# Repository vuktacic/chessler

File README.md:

# chessler/chessbot
A robot that plays chess. It uses a camera to detect Aruco tags on the board corners and the pieces, and an electromagnet on a gantry under the board to move the pieces. Designed for Hack Club's Outpost program. I wanted to do something involving Aruco tags outside of FRC, and this seemed like a good project to make.

## Structure
- [./assets](./assets): Repo images
- [./cad](./cad): 3d models
- [./core](./core): esp32 firmware
- [./pcb](./pcb): Kicad design files.
- [./vision](./vision): Computer side vision code
- [./bom.csv](./bom.csv): Bill of materials
- [./po.csv](./po.csv): Purchase order
- [./JOURNAL.md](./JOURNAL.md): Project journal

View the PCB on KiCanvas:  

## CAD

## Schematic

## PCB

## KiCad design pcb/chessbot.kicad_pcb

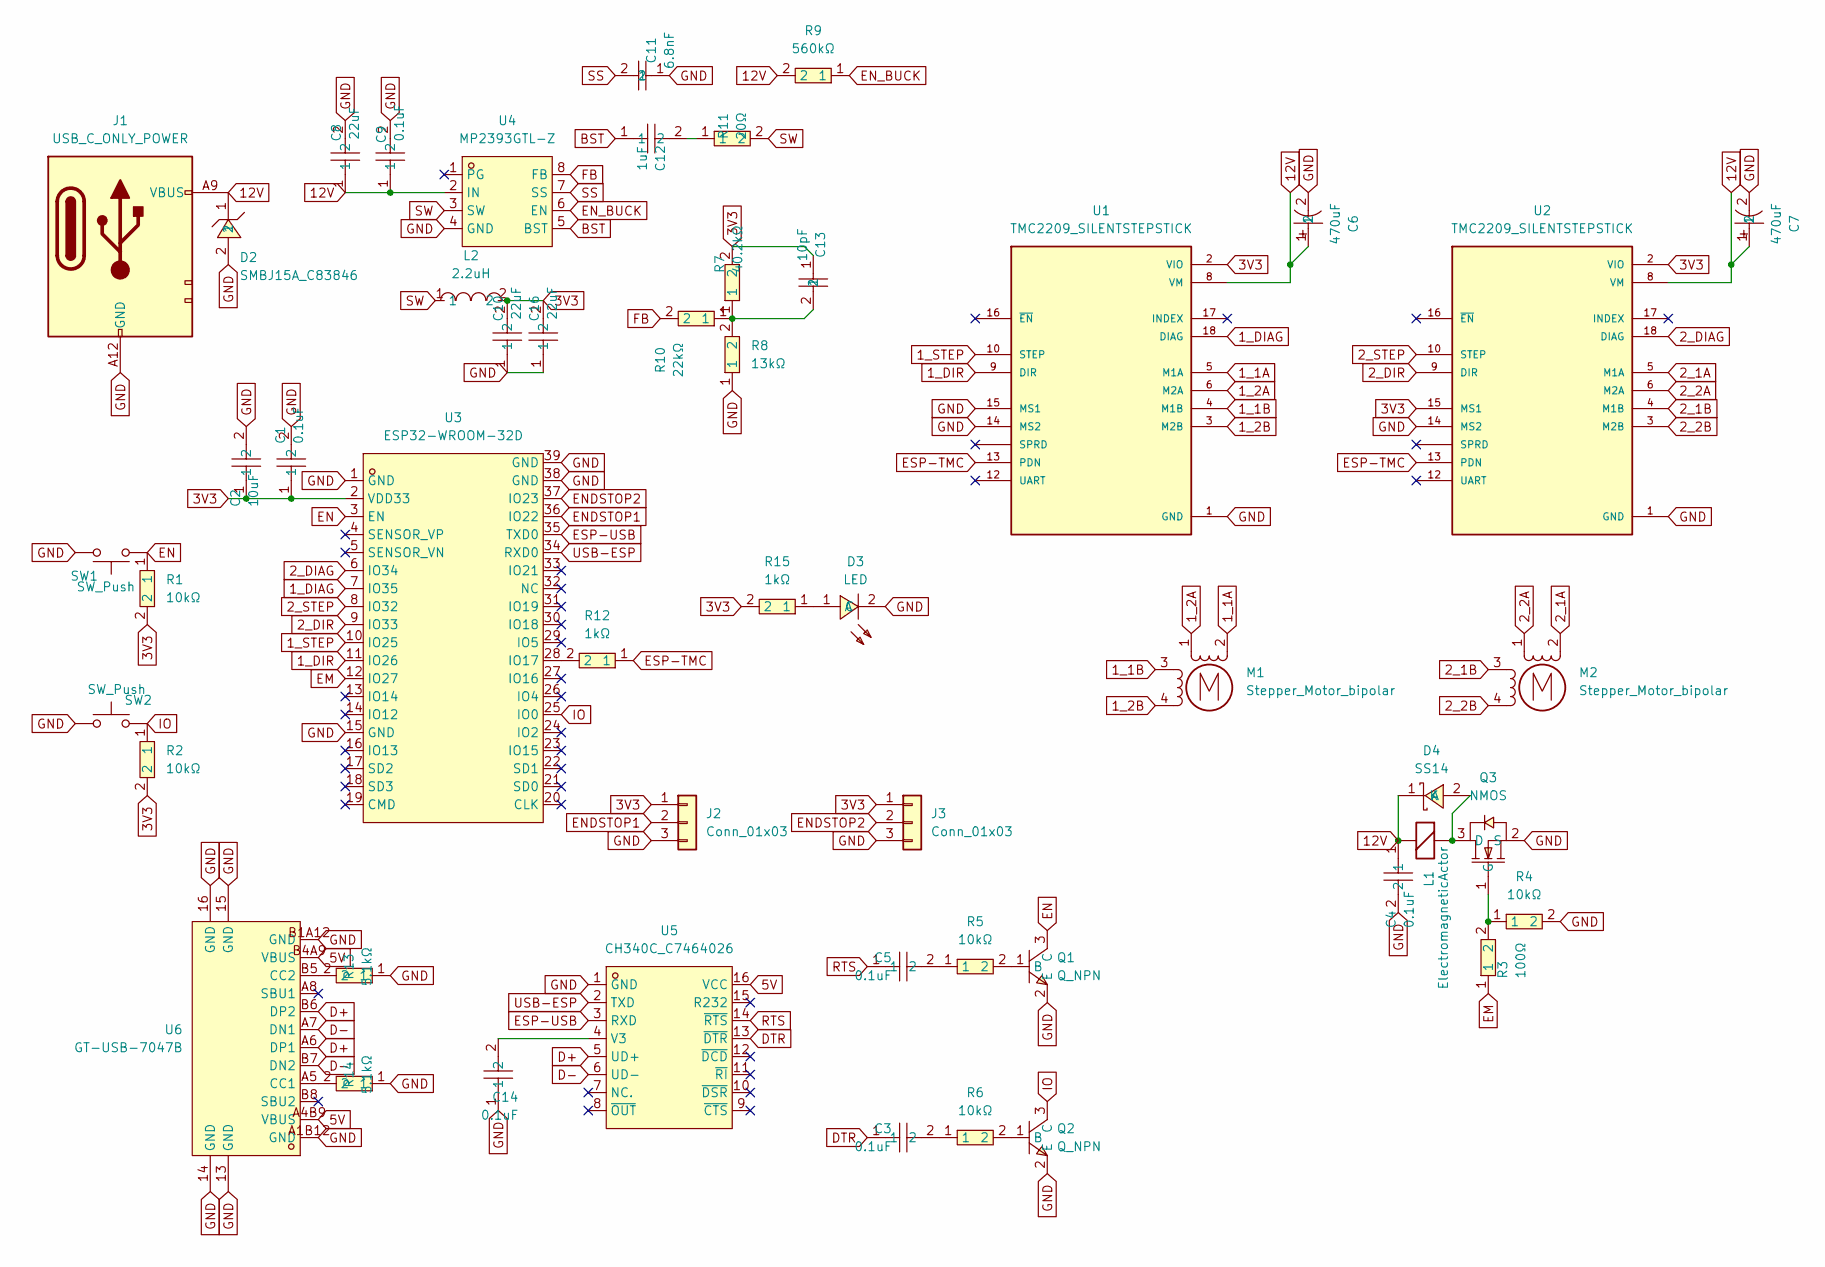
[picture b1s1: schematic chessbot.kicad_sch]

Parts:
C1, C3, C4, C5, C9, C14: 0.1uF; C0603; MPN CC0603KRX7R9BB104; LCSC Part C14663
C2: 10uF; C0603; MPN CL10A106MA8NRNC; LCSC Part C96446
C6, C7: 470uF; CAP-SMD_BD10.0-L10.3-W10.3-FD; MPN RVT1V471M1010; LCSC Part C3350
C8, C10, C16: 22uF; C0805; MPN CL21A226MAQNNNE; LCSC Part C45783
C11: 6.8nF; C0603; MPN 0603B682K500NT; LCSC Part C1631
C12: 1uF; C0603; MPN CL10A105KB8NNNC; LCSC Part C15849
C13: 10pF; C0603; MPN CL10C100JB8NNNC; LCSC Part C1634
D2: SMBJ15A_C83846; SMB_L4.6-W3.6-LS5.3-RD; LCSC Part C83846
D3: LED; LED0603-R-RD_AMBER; MPN BL-HJC36G-AV-TRB; LCSC Part C165983
D4: SS14; SMA_L4.2-W2.6-LS5.0-RD_1; MPN SS14; LCSC Part C2480
J1: USB_C_ONLY_POWER; USB_C_PD_BOARD
J2, J3: Conn_01x03; JST_PH_B3B-PH-K_1x03_P2.00mm_Vertical
L1: ElectromagneticActor; JST_PH_B2B-PH-K_1x02_P2.00mm_Vertical
L2: 2.2uH; L0805; MPN CMI201209U2R2KT; LCSC Part C1043
M1, M2: Stepper_Motor_bipolar; JST_PH_B4B-PH-K_1x04_P2.00mm_Vertical
Q1, Q2: Q_NPN; SOT-23-3_L2.9-W1.3-P1.90-LS2.4-BR; MPN MMBT3904(RANGE:100-300); LCSC Part C20526
Q3: NMOS; SOT-23-3_L2.9-W1.3-P1.90-LS2.4-BR; MPN AO3400A; LCSC Part C20917
R1, R2, R4, R5, R6: 10kΩ; R0805; MPN 0805W8F1002T5E; LCSC Part C17414
R3: 100Ω; R0603; MPN 0603WAF1000T5E; LCSC Part C22775
R7: 40.2kΩ; R0603; MPN 0603WAF4022T5E; LCSC Part C12447
R8: 13kΩ; R0603; MPN 0603WAF1302T5E; LCSC Part C22797
R9: 560kΩ; R0603; MPN 0603WAF5603T5E; LCSC Part C23203
R10: 22kΩ; R0603; MPN 0603WAF2202T5E; LCSC Part C31850
R11: 20Ω; R0603; MPN 0603WAF200JT5E; LCSC Part C22950
R12, R15: 1kΩ; R0603; MPN 0603WAF1001T5E; LCSC Part C21190
R13, R14: 5.1kΩ; R0603; MPN 0603WAF5101T5E; LCSC Part C23186
SW1, SW2: SW_Push; SW_PUSH_6mm
U1, U2: TMC2209_SILENTSTEPSTICK; MODULE_TMC2209_SILENTSTEPSTICK_INTERNAL SILKSCREEN; PARTREV 1.20
U3: ESP32-WROOM-32D; WIFIM-SMD_39P-L25.5-W18.0-P1.27-BL; MPN ESP32-WROOM-32D-N4; LCSC Part C529578
U4: MP2393GTL-Z; SOT-583-8_L2.1-W1.2-P0.50-LS1.6-BL; MPN MP2393GTL-Z; LCSC Part C6674609
U5: CH340C_C7464026; SOP-16_L10.0-W3.9-P1.27-LS6.0-BL; MPN CH340C; LCSC Part C7464026
U6: GT-USB-7047B; MICRO-USB-SMD_GT-USB-7047B; MPN GT-USB-7047B; LCSC Part C963217

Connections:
1_1A: M1.2 (-_2), U1.5 (M1A)
1_1B: M1.3, U1.4 (M1B)
1_2A: M1.1, U1.6 (M2A)
1_2B: M1.4, U1.3 (M2B)
1_DIAG: U1.18 (DIAG), U3.7 (IO35)
1_DIR: U1.9 (DIR), U3.11 (IO26)
1_STEP: U1.10 (STEP), U3.10 (IO25)
2_1A: M2.2 (-_2), U2.5 (M1A)
2_1B: M2.3, U2.4 (M1B)
2_2A: M2.1, U2.6 (M2A)
2_2B: M2.4, U2.3 (M2B)
2_DIAG: U2.18 (DIAG), U3.6 (IO34)
2_DIR: U2.9 (DIR), U3.9 (IO33)
2_STEP: U2.10 (STEP), U3.8 (IO32)
3V3: C1.1, C2.1, C10.2, C13.1, C16.2, J2.1, J3.1, L2.2, R1.2, R2.2, R7.2, R15.2, U1.2 (VIO), U2.2 (VIO), U2.15 (MS1), U3.2 (VDD33)
5V: U5.16 (VCC), U6.A4B9 (VBUS), U6.B4A9 (VBUS)
12V: C4.1, C6.1, C7.1, C8.1, C9.1, D2.1, D4.1 (K), J1.A9 (VBUS), L1.2 (+), R9.2, U1.8 (VM), U2.8 (VM), U4.2 (IN)
BST: C12.1, U4.5 (BST)
D+: U5.5 (UD+), U6.A6 (DP1), U6.B6 (DP2)
D-: U5.6 (UD-), U6.A7 (DN1), U6.B7 (DN2)
DTR: C3.1, U5.13 (~DTR)
EM: R3.1, U3.12 (IO27)
EN: Q1.3 (C), R1.1, SW1.1, U3.3 (EN)
ENDSTOP1: J2.2, U3.36 (IO22)
ENDSTOP2: J3.2, U3.37 (IO23)
EN_BUCK: R9.1, U4.6 (EN)
EN_TMC: U1.16 (~EN), U2.16 (~EN)
ESP-TMC: R12.1, U1.13 (PDN), U2.13 (PDN)
ESP-USB: U3.35 (TXD0), U5.3 (RXD)
FB: R10.2, U4.8 (FB)
GND: C1.2, C2.2, C4.2, C6.2, C7.2, C8.2, C9.2, C10.1, C11.1, C14.1, C16.1, D2.2, D3.2 (C), J1.A12 (GND), J2.3, J3.3, Q1.2 (E), Q2.2 (E), Q3.2 (S), R4.2, R8.1, R13.1, R14.1, SW1.2, SW2.1, U1.1 (GND), U1.7 (GND), U1.14 (MS2), U1.15 (MS1), U2.1 (GND), U2.7 (GND), U2.14 (MS2), U3.1 (GND), U3.15 (GND), U3.38 (GND), U3.39 (GND), U4.4 (GND), U5.1 (GND), U6.13 (GND), U6.14 (GND), U6.15 (GND), U6.16 (GND), U6.A1B12 (GND), U6.B1A12 (GND)
IO: Q2.3 (C), R2.1, SW2.2, U3.25 (IO0)
unnamed: C3.2, R6.1
unnamed: C5.2, R5.1
unnamed: C12.2, R11.1
unnamed: C13.2, R7.1, R8.2, R10.1
unnamed: D3.1 (A), R15.1
unnamed: D4.2 (A), L1.1 (-), Q3.3 (D)
unnamed: Q1.1 (B), R5.2
unnamed: Q2.1 (B), R6.2
unnamed: Q3.1 (G), R3.2, R4.1
unnamed: R12.2, U3.28 (IO17)
unnamed: C14.2, U5.4 (V3)
unnamed: R14.2, U6.A5 (CC1)
unnamed: R13.2, U6.B5 (CC2)
RTS: C5.1, U5.14 (~RTS)
SS: C11.2, U4.7 (SS)
SW: L2.1, R11.2, U4.3 (SW)
USB-ESP: U3.34 (RXD0), U5.2 (TXD)

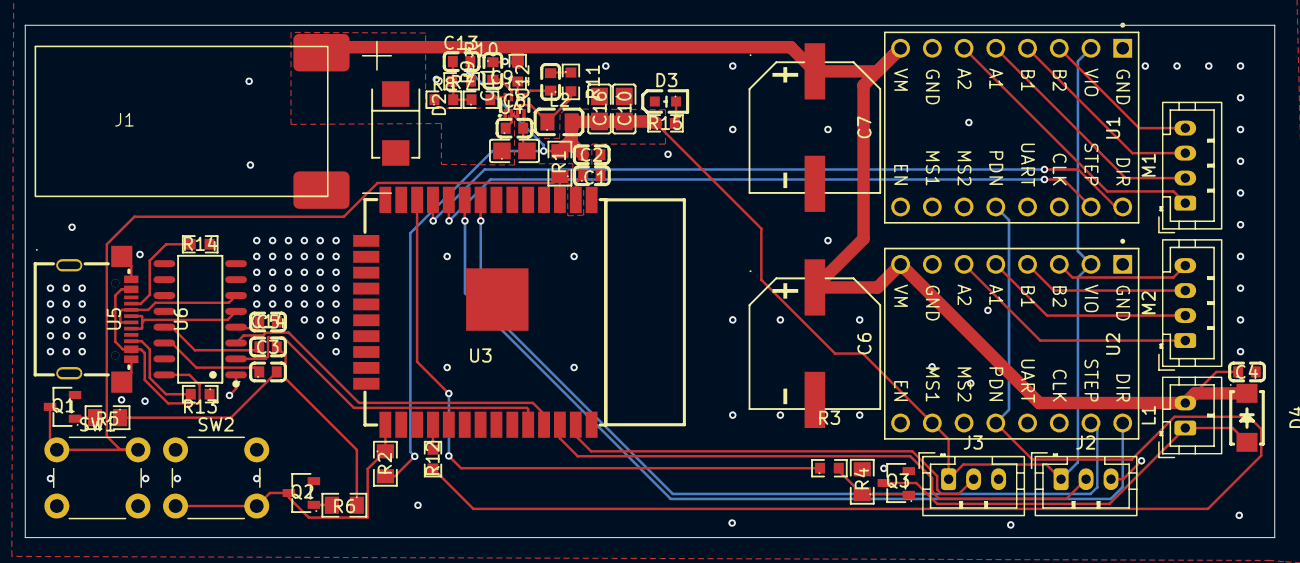
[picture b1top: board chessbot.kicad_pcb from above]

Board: 2 copper layers, 100.0 x 41.0 mm, 51 parts (0 on the bottom side), 47 nets.

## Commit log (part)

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2026-06-14 Create LICENSE
2026-06-14 Setup repo
2026-06-14 CAD begin
2026-06-14 Add .gitattributes
2026-06-15 Journalling for yesterday: fusion cad & kicad schematic
2026-06-15 Update kicad gitignore
2026-06-16 Journal for yesterday: jlc component sourcing
2026-06-17 PCB routing
2026-06-18 Major CAD progress
2026-06-25 Journal for 23rd
2026-06-25 Finish cad
2026-06-25 Forgot to add image
2026-06-26 Most of the firmware & board fen from aruco tags
2026-06-26 Firmware
